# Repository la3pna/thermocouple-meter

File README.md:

View this project on [CADLAB.io](https://cadlab.io/project/1066). 

# thermocouple-meter
a open source thermocouple meter

This project runs on the Empyrean series ARM microcontroller boards. It may run on Arduino Zero and other SAMD series, but it will not run on ATMEGA series boards!

Todo:
PCB:
* do a PCB for the 2 sensors 3 and 4
* ESP-01 wlan alternative? (as of now there is a extra serial on the board.)
* GPIB? (using the extra serial port?)

SCPI Commands:
   *  *IDN?                  -> identify
   *  *RST                   -> reset to local
   *  :TRIGger
       *    :SINGle          -> trigger single
       *    :CONTinous       -> trigger continous
   *  :MEASure
       *    :TEMPerature?    -> get all temp
       *    :TEMPerature1?   -> get temp1
       *    :TEMPerature2?   -> get temp2
       *    :TEMPerature3?   -> get temp3
       *    :TEMPerature4?   -> get temp4
       *    :INTernal1?      -> get int1 (compensation temperature)
       *    :INTernal2?      -> get int2
       *    :INTernal3?      -> get int3
       *    :INTernal4?      -> get int4
   *  :SYStem
       *    :VOLTage?        -> get supply voltage
       *    :ERRor?          -> get/clears error from error handling
       *    :PRINT           -> display print string
   *  :UNIT *(getting these to work will require rewriting the adafruit library from scratch)*
       *    :TEMPerature     -> set_temperature_unit (C/CEL/F/FAR/K/KEL) *NOT IMPLEMENTED YET* 
       *    :TEMPerature?    -> get_temprature unit (C/CEL/F/FAR/K/KEL) *NOT IMPLEMENTED YET*
       
 Libraries needed: 
   - U8g2lib (Available in arduino library manager)
   - Open Instrument control [scpiparser] ( https://github.com/la3pna/oic )
   - Adafruit MAX31855 (available in arduino library manager) (intend to rewrite this to use some SAMD features in getting the data) 
   
   Bevare that there is some fake MAX31855 on the marked that does not work! Make sure you get your MAX31855 and thermocouples from a reputable source to avoid problems.

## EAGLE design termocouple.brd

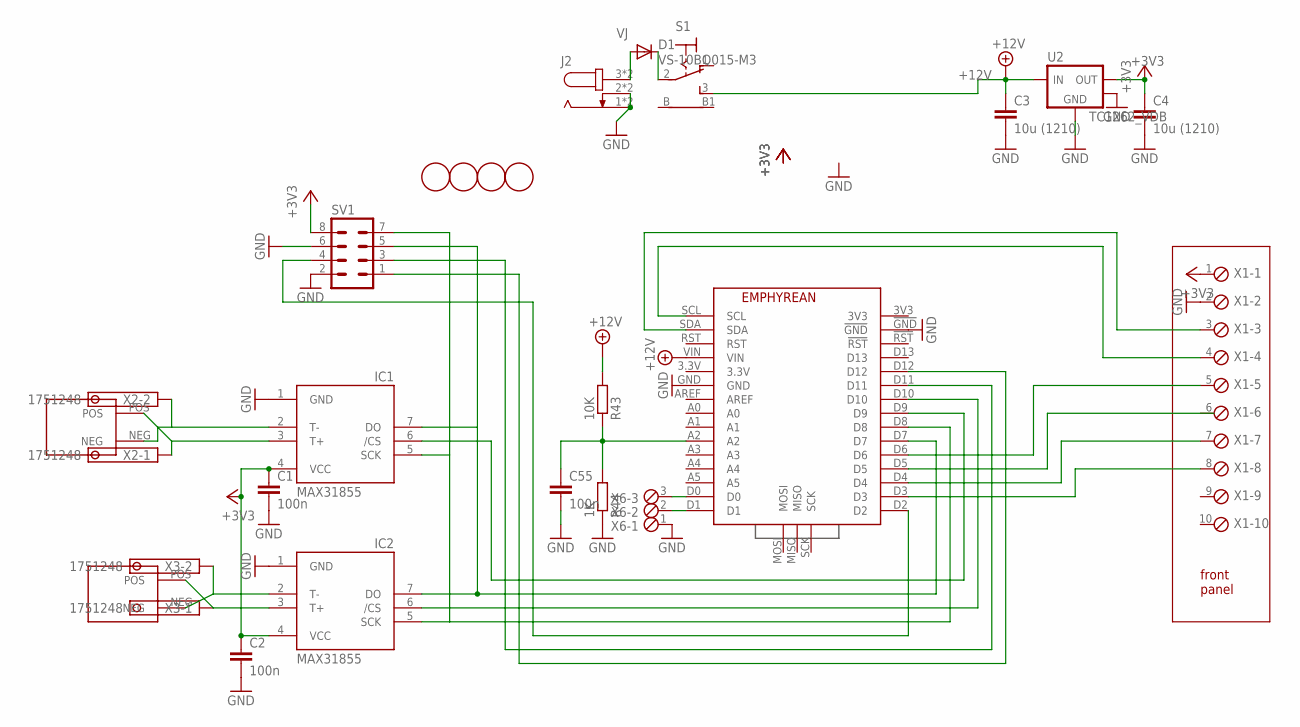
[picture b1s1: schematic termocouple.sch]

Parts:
C1, C2, C55: 100n; C1206
C3, C4: 10u (1210); C1210
D1: VS-10BQ015-M3; SMB
IC1, IC2: MAX31855; SO08
J2: JACK-PLUG; SPC4078
R43: 10K; R1206
R44: 1K; R1206
S1: LPV-1
SV1: MA04-2
U2: TC1262_VDB; SOT-223-3
U$1: EPHYREAN; EMPHYREAN
U$2, U$3: THERMOCOUPLE
U$4, U$5, U$6, U$7: FIDUCIAL; FIDUCIAL_1MM
X1: MPT10; 10POL254
X2, X3: 1751248
X6: MPT3; 3POL254

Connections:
+3V3: C1.1, C2.1, C4.1, IC1.4 (VCC), IC2.4 (VCC), SV1.8, U2.3 (VOUT), X1.1
+12V: C3.1, R43.2, S1.3 (S), U2.1 (VIN), U$1.VIN
GND: C1.2, C2.2, C3.2, C4.2, C55.2, IC1.1 (GND), IC2.1 (GND), J2.1, J2.2, J2.4 (1), J2.5 (2), R44.1, SV1.2, SV1.6, U2.2 (GND), U2.4 (TAB), U$1.!GND, U$1.GND, X1.2, X6.1
unnamed: IC1.7 (DO), IC2.7 (DO), SV1.5, U$1.D7
unnamed: IC1.5 (SCK), IC2.5 (SCK), SV1.7, U$1.D8
unnamed: IC2.6 (/CS), U$1.D10
unnamed: IC1.6 (/CS), U$1.D9
unnamed: U$1.SDA, X1.3
unnamed: SV1.3, U$1.D11
unnamed: U$1.SCL, X1.4
unnamed: U$1.D6, X1.5
unnamed: U$1.D4, X1.7
unnamed: U$1.D3, X1.8
unnamed: D1.C, S1.2
unnamed: SV1.1, U$1.D12
unnamed: SV1.4, U$1.D2
unnamed: IC2.3 (T+), U$2.POS, X3.1
unnamed: IC2.2 (T-), U$2.NEG, X3.2
unnamed: IC1.3 (T+), U$3.POS, X2.1
unnamed: IC1.2 (T-), U$3.NEG, X2.2
unnamed: U$1.D0, X6.3
unnamed: U$1.D1, X6.2
unnamed: C55.1, R43.1, R44.2, U$1.A2
VJ: D1.A, J2.3, J2.6 (3)

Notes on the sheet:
front panel

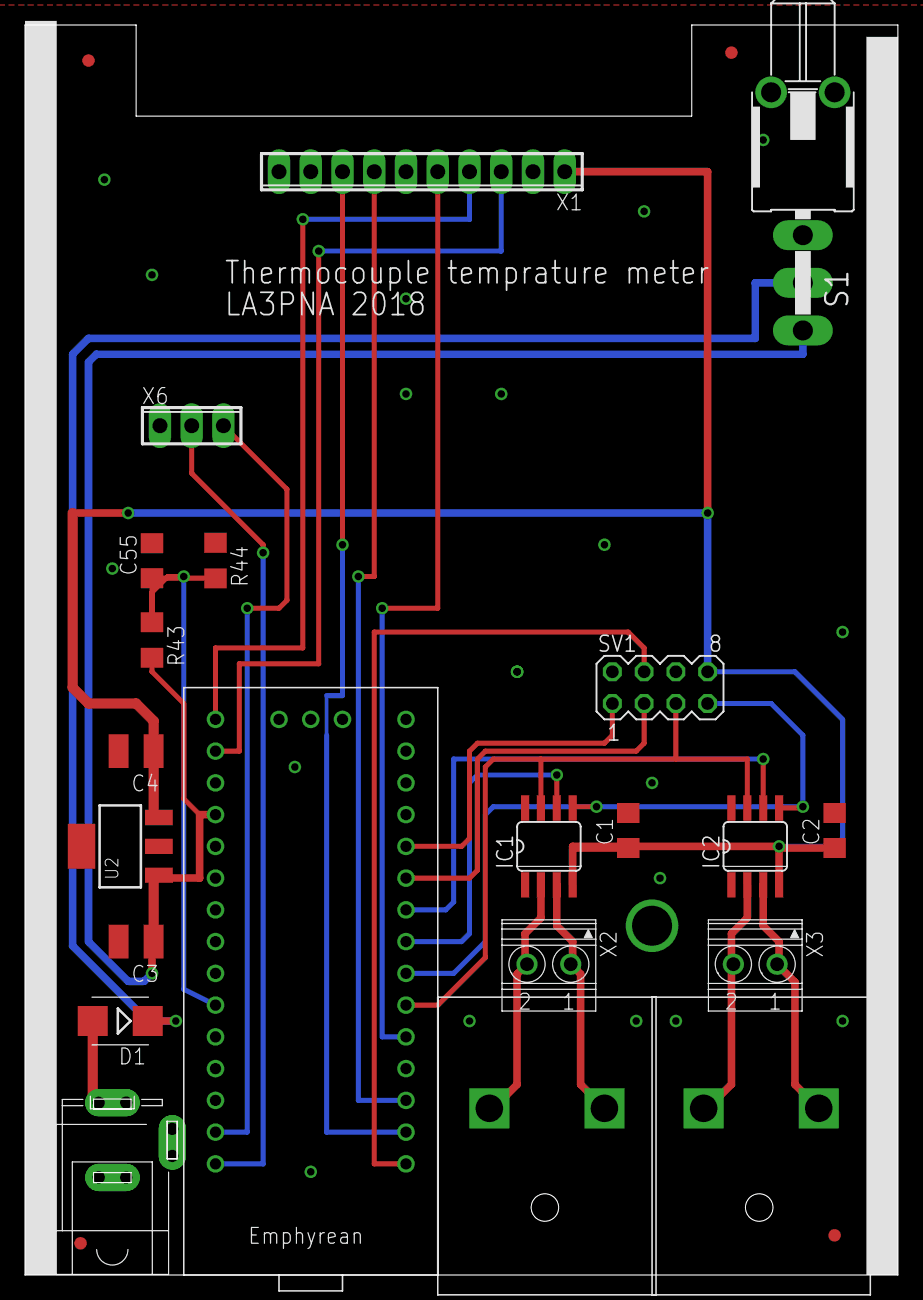
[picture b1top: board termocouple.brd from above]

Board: 2 copper layers, 69.8 x 100.0 mm, 25 parts (0 on the bottom side), 24 nets.

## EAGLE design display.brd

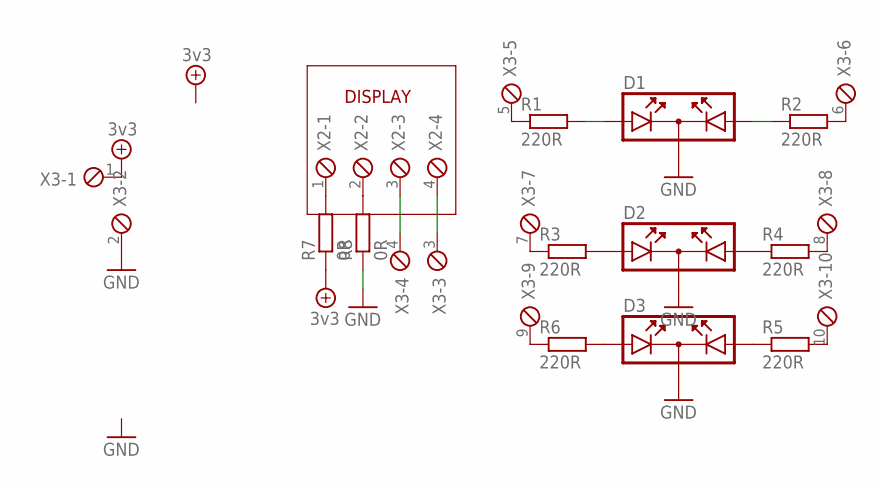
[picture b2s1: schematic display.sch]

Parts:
D1, D2, D3: DUOLED
R1, R2, R3, R4, R5, R6: 220R; R0603
R7, R8: 0R; R0603
X2: MPT4; 4POL254
X3: MPT10; 10POL254

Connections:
+UB: R7.1, X3.1
GND: D1.K, D2.K, D3.K, R8.1, X3.2
unnamed: D1.A1, R1.2
unnamed: D1.A2, R2.1
unnamed: X2.3, X3.4
unnamed: X2.4, X3.3
unnamed: R1.1, X3.5
unnamed: R2.2, X3.6
unnamed: D2.A1, R3.2
unnamed: D2.A2, R4.1
unnamed: D3.A2, R5.1
unnamed: D3.A1, R6.2
unnamed: R3.1, X3.7
unnamed: R4.2, X3.8
unnamed: R6.1, X3.9
unnamed: R5.2, X3.10
unnamed: R7.2, X2.1
unnamed: R8.2, X2.2

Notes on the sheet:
DISPLAY

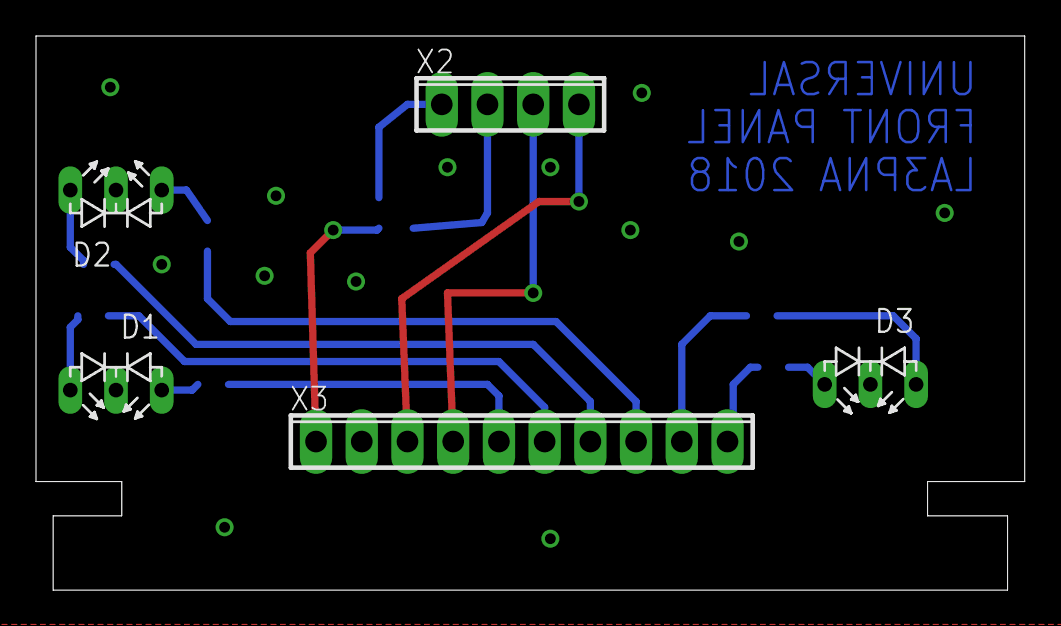
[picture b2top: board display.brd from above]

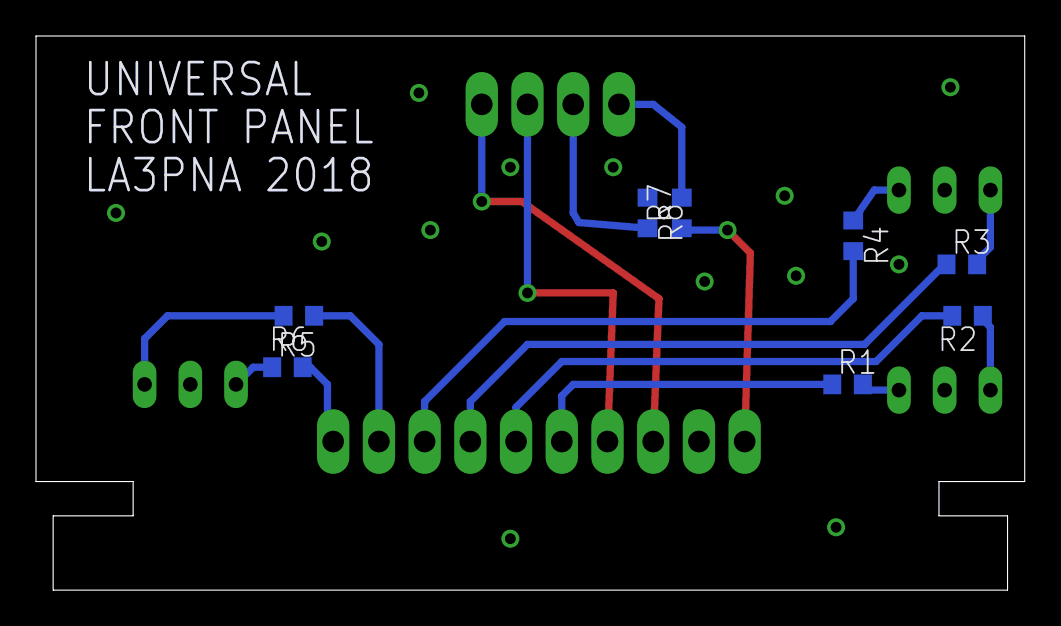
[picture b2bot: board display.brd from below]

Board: 2 copper layers, 54.9 x 30.8 mm, 13 parts (8 on the bottom side), 18 nets.

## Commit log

2018-05-21 eagle files
2018-05-21 Backlink to CADLAB.io has been added.
2018-05-21 arduino program
2018-05-21 update brd
2018-05-21 sch update
2018-05-21 brd
    power supply measuring, should do somthing with the rest of the adc pins?
2018-05-21 test ignore
2018-05-21 fix gitignore
2018-05-21 wiring change
2018-05-21 del b# files
2018-05-21 front panel + brd traces
2018-05-21 firmware changed to include u8g2 for display
2018-05-22 u8glib2 + firmware changes, added scpi
2018-05-22 FW: changes in font and printing
2018-05-22 BRD added thermocouple device
    thermocouple
2018-05-22 scpi
2018-05-24 readme update, arm definitions, pcb moved to 2 sensor
2018-05-27 comments changed
2018-05-27 started a implementation of serial switching
    Implement answering serials, also some SCPI FIX
2018-05-27 fix SCPI things, switching between serials
2018-05-27 definition changes, more SCPI
2018-05-27 added error handling
2018-05-27 updated brd
    finished routing PCB
2018-05-28 fix typo
2018-05-29 front panel board made to fit
2018-06-01 fix switching between 2 and 4 sensors
2018-06-01 fix of the verbose spewing out data like its getting paid for it
2018-06-01 small rework to remove the sensor 3 and 4 SCPI from a board with 2 sensors
2018-06-01 figuring out how to use the SCPI library, need to do a string parser...
2018-06-01 print routine added
2018-06-02 licence and header
2018-06-02 fix multiple serial port logic
2018-06-03 remove some unneeded commented lines
2018-06-12 error in verbose output
2018-06-24 buildinstructions
2018-06-24 markdown
2018-08-20 pdf version of schematics
2018-12-02 pcb fix
    Fix PCB's to make it possible to build the boards without rework
2018-12-02 program changes
    Add resistor for voltage dividers
2018-12-02 fix readout
2018-12-03 update display.brd and thermocouple
2019-02-08 pcb add fiducials
2019-02-10 UF2 binary for Alpha
